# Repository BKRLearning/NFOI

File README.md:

****
# Kitchen Mania
****
Kitchen Mania uses screen-based game control as a starting point for understanding and exploring new methods of interacting with physical computer interfaces. It uses familiar household appliances and tools to produce novel forms of human-computer interaction that are intuitive and accessible.

One the primary goals of Kitchen Mania is to achieve functional human interface devices that simultaneously perform real physical tasks. While playful, we believe these controllers show the viability of highly accurate / low latency passive sensing of existing electronic appliances. This work has applications in a range of smart home and IoT use cases.

Setup
=========
Lorem ipsum dolor sit amet, consectetur adipiscing elit, sed do eiusmod tempor incididunt ut labore et dolore magna aliqua. Ut enim ad minim veniam, quis nostrud exercitation ullamco laboris nisi ut aliquip ex ea commodo consequat. Duis aute irure dolor in reprehenderit in voluptate velit esse cillum dolore eu fugiat nulla pariatur. Excepteur sint occaecat cupidatat non proident, sunt in culpa qui officia deserunt mollit anim id est laborum.

PulpPad
=========
The PulpPad is a controller comprised of four electric juicers with interchangeable button mapping. For this demo, we have setup two PulpPads mapped in a D-pad configuration to StepMania, a Dance Dance Revolution simulator. Hand-dance battle your friends and drink some freshly squeezed juice after you play!

conROLLER
=========
The conROLLER is a rolling pin controller designed to work with single-axis games. Roll the pin to move your player on screen // use the thumb button to fire and activate the two attached relays. Fire up your pizza oven and make some own pizza after destroying enemy ships!

Project resources
=================
- [Website](http://www.brooklynresearch.org)
- [Source code](#)
- [Scematics](https://github.com/BKRLearning/NFOI/tree/master/Schematics)

License
=======
Copyright 2018 Brooklyn Research and contributors.
Licensed under MIT, Version 2.0. See the file LICENSE for the full license text.

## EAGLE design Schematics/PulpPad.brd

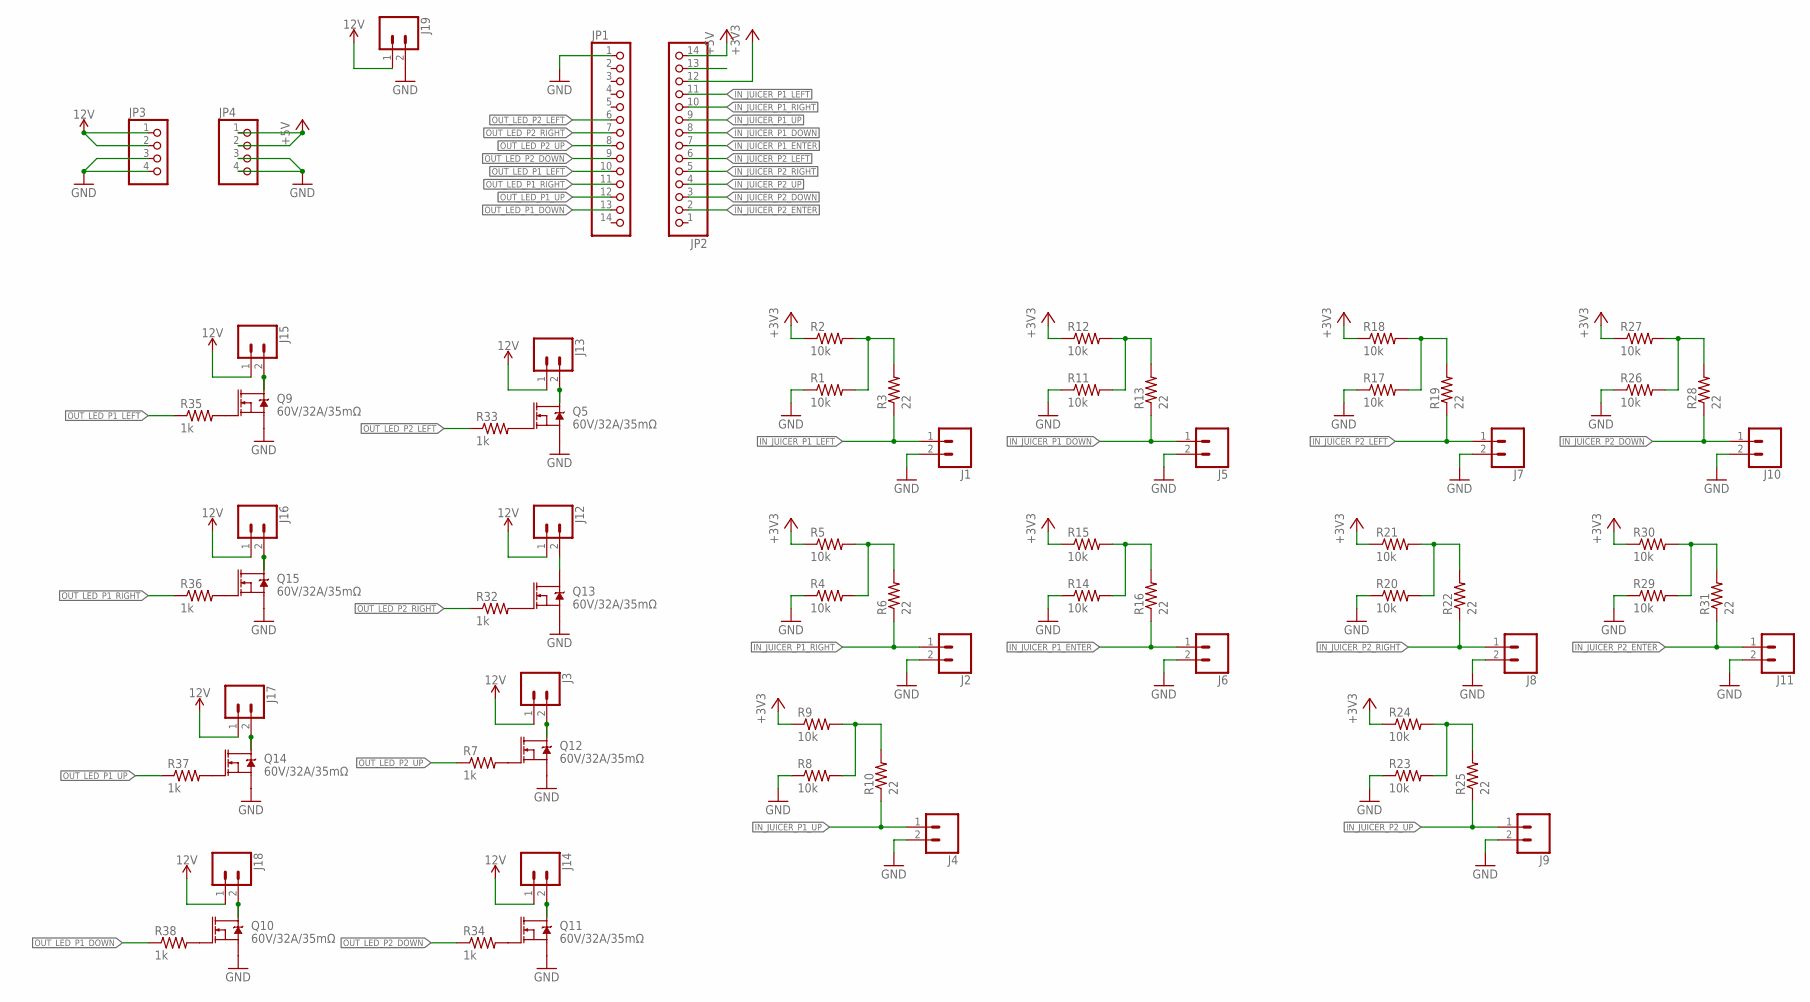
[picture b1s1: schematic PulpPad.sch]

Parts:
J1, J2, J3, J4, J5, J6, J7, J8, J9, J10, J11, J12, J13, J14, J15, J16, J17, J18, J19: CONN_023.5MM; SCREWTERMINAL-3.5MM-2
JP1, JP2: PINHD-1X14; 1X14
JP3, JP4: PINHD-1X4; 1X04
Q5, Q9, Q10, Q11, Q12, Q13, Q14, Q15: 60V/32A/35mΩ; TO220V
R1, R2, R4, R5, R8, R9, R11, R12, R14, R15, R17, R18, R20, R21, R23, R24, R26, R27, R29, R30: 10k; 0204/7
R3, R6, R10, R13, R16, R19, R22, R25, R28, R31: 22; 0204/7
R7, R32, R33, R34, R35, R36, R37, R38: 1k; 0204/7

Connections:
12V: J3.1, J12.1, J13.1, J14.1, J15.1, J16.1, J17.1, J18.1, J19.1, JP3.1, JP3.2
+3V3: JP2.12, R2.1, R5.1, R9.1, R12.1, R15.1, R18.1, R21.1, R24.1, R27.1, R30.1
+5V: JP2.14, JP4.1, JP4.2
GND: J1.2, J2.2, J4.2, J5.2, J6.2, J7.2, J8.2, J9.2, J10.2, J11.2, J19.2, JP1.1, JP3.3, JP3.4, JP4.3, JP4.4, Q5.3 (S), Q9.3 (S), Q10.3 (S), Q11.3 (S), Q12.3 (S), Q13.3 (S), Q14.3 (S), Q15.3 (S), R1.1, R4.1, R8.1, R11.1, R14.1, R17.1, R20.1, R23.1, R26.1, R29.1
IN_JUICER_P1_DOWN: J5.1, JP2.8, R13.1
IN_JUICER_P1_ENTER: J6.1, JP2.7, R16.1
IN_JUICER_P1_LEFT: J1.1, JP2.11, R3.1
IN_JUICER_P1_RIGHT: J2.1, JP2.10, R6.1
IN_JUICER_P1_UP: J4.1, JP2.9, R10.1
IN_JUICER_P2_DOWN: J10.1, JP2.3, R28.1
IN_JUICER_P2_ENTER: J11.1, JP2.2, R31.1
IN_JUICER_P2_LEFT: J7.1, JP2.6, R19.1
IN_JUICER_P2_RIGHT: J8.1, JP2.5, R22.1
IN_JUICER_P2_UP: J9.1, JP2.4, R25.1
unnamed: R1.2, R2.2, R3.2
unnamed: Q15.1 (G), R36.2
unnamed: J3.2, Q12.2 (D)
unnamed: R8.2, R9.2, R10.2
unnamed: R4.2, R5.2, R6.2
unnamed: R11.2, R12.2, R13.2
unnamed: R14.2, R15.2, R16.2
unnamed: R17.2, R18.2, R19.2
unnamed: R20.2, R21.2, R22.2
unnamed: R23.2, R24.2, R25.2
unnamed: R26.2, R27.2, R28.2
unnamed: R29.2, R30.2, R31.2
unnamed: Q14.1 (G), R37.2
unnamed: J12.2, Q13.2 (D)
unnamed: Q10.1 (G), R38.2
unnamed: J13.2, Q5.2 (D)
unnamed: Q5.1 (G), R33.2
unnamed: J14.2, Q11.2 (D)
unnamed: Q9.1 (G), R35.2
unnamed: J15.2, Q9.2 (D)
unnamed: Q13.1 (G), R32.2
unnamed: J16.2, Q15.2 (D)
unnamed: Q12.1 (G), R7.2
unnamed: J17.2, Q14.2 (D)
unnamed: Q11.1 (G), R34.2
unnamed: J18.2, Q10.2 (D)
OUT_LED_P1_DOWN: JP1.13, R38.1
OUT_LED_P1_LEFT: JP1.10, R35.1
OUT_LED_P1_RIGHT: JP1.11, R36.1
OUT_LED_P1_UP: JP1.12, R37.1
OUT_LED_P2_DOWN: JP1.9, R34.1
OUT_LED_P2_LEFT: JP1.6, R33.1
OUT_LED_P2_RIGHT: JP1.7, R32.1
OUT_LED_P2_UP: JP1.8, R7.1

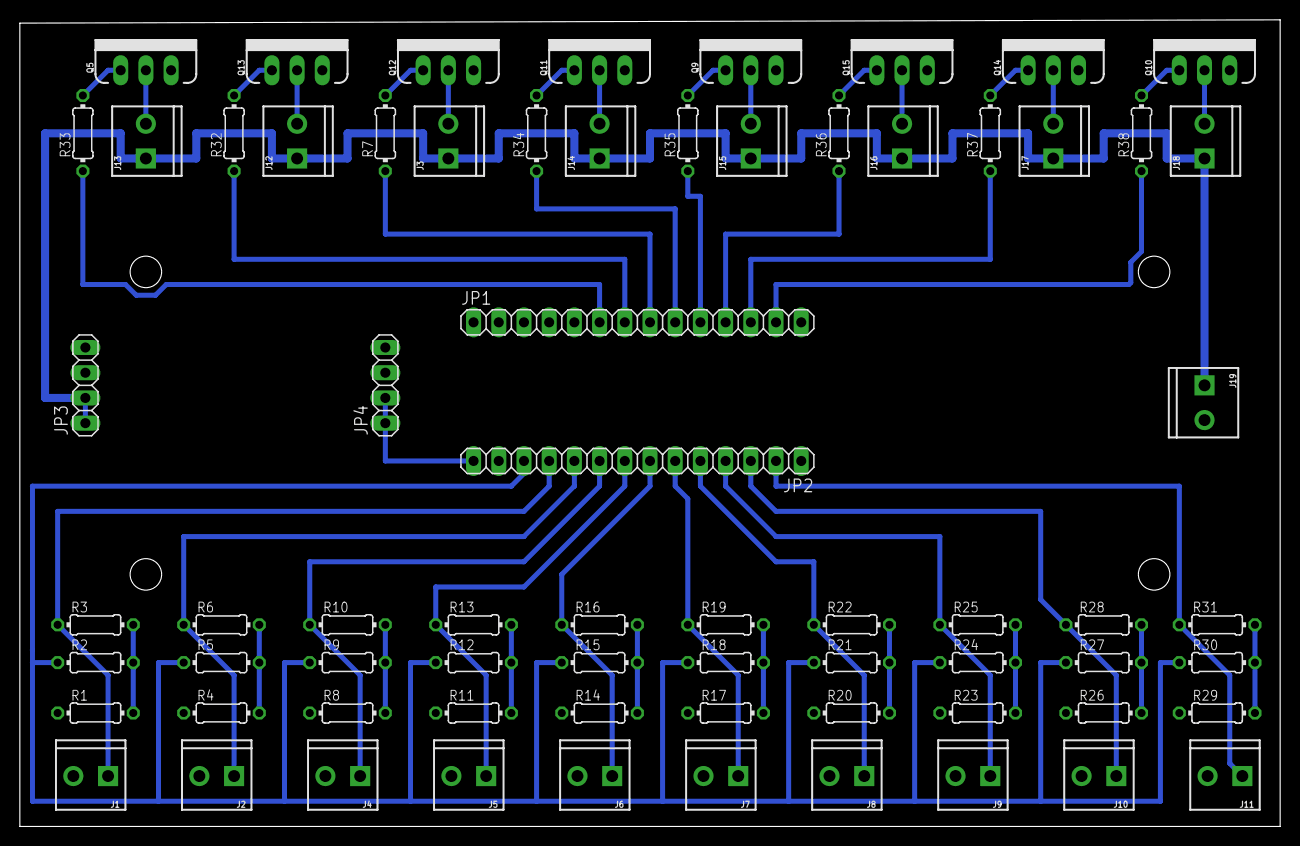
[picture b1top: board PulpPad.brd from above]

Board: 2 copper layers, 127.0 x 81.3 mm, 69 parts (0 on the bottom side), 48 nets.

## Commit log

2018-07-23 Add folder structure, push rolling pin code
2018-07-23 Create Juicer
2018-07-23 Added juicer code w/ averaging
2018-07-23 Updated vars in multiple juicer code
2018-07-23 Updated averaging code
2018-07-23 Updated current multi averaging code
2018-07-24 added additional comments for clarity
2018-07-30 added 2nd blender, updated delay structure
2018-07-30 restructured code as individual functions, added comments
2018-07-31 Create license
2018-08-05 add juicer with led code
2018-08-14 Added sketch with 2P & LEDs
2018-08-14 Updated enter button code, added additional comments
2018-08-14 Fixed button key presses, added comments
2018-08-22 Fixed enter buttons, updated delay
2018-09-21 Added PulpPad schematics, reorg code
2018-09-22 Updated conROLLER folders

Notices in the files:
parts and their libraries:
SparkFun-Connectors: Licensing: Creative Commons ShareAlike 4.0 International - https://creativecommons.org/licenses/by-sa/4.0
